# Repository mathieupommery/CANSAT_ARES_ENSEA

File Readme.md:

# Projet 2A CanSat 2024-2025 🚀

## Table des Matières

- [Introduction](#introduction)
- [Équipe](#équipe)
- [Journal de bord](#journal-de-bord)
   - [Objectifs](#objectifs)
- [Livrable](#livrables)
   - [PCB](#pcb)
   - [Station sol](#station-sol)

---

## Introduction
- Il s'agit d'un projet de 2e année d'école d'ingénieur en électronique à l'[ENSEA](https://www.ensea.fr/fr) à Cergy.
- Le but étant de réaliser - pour la **compétition CanSat** organisée par **Planète Sciences et le CNES** - un satellite en forme de canette.
- Celui-ci devra **réaliser plusieurs missions** lorsqu'il sera **lâché d'un drone à environ 120m de hauteur devant un jury**.
- Le projet consiste à faire la **conception** et la **fabrication** de ce satellite.
   - Partie électronique
   (PCB, capteurs, alimentation, station au sol,... )
   - Partie mécanique
   (Châssis, taille, matériau,... )
   - Partie résultats
   (Exploitation des mesures, les mettre en forme en développant ou non une interface, les présenter devant le jury,... )
- Les 4 missions principales imposées en plus du règlement sont :
   - **Mission 1 : Séparation & Transmission**
      - Le CanSat doit se séparer en deux parties à une altitude comprise entre 40 et 60 mètres.​
      - La chaîne de séparation doit résister à une traction de 30N.​
      - Transmission : ​une des parties du CanSat doit transmettre l'altitude et une donnée sur l'atmosphère en temps réel vers une station sol.
   - **Mission 2 : Rétrécissement​**
      - Réduire le CanSat au format 33 cl vous permettra de multiplier votre score par 2 sur la partie technique.
   - **Mission 3 : Instrumentation cassée​**
      - Trouvez un moyen de déterminer votre altitude à partir d'un capteur autre qu'un altimètre barométrique ou un GPS.
   - **Mission 4 : Distance​**
      - Intégrez de quoi mesurer la distance entre les deux parties du CanSat et la communiquer par télémétrie vers la station sol.
      - La Mission 3 n'intervient pas ici.

## Équipe

<div align="center">

   **🙋‍♂️ [Hugo CARVALHO FONTES](https://github.com/HugouShare)**

   **🙋‍♂️ [Louis VOZZOLA](https://github.com/louisvoz57700)**

   **🙋‍♂️ [Nelven THÉBAULT](https://github.com/NelvTheb)**

   **🙋‍♂️ [Mathieu POMMERY](https://github.com/mathieupommery)**

   **🙋‍♂️ [Younés BEN AMEUR](https://github.com/younsben)**

</div>

## Journal de bord

### Présentation orale
- Vous pouvez trouver ici le lien en consultation de l'ensemble de nos [présentations orales](https://enseafr-my.sharepoint.com/:p:/g/personal/nelven_thebault_ensea_fr/EQFq_InugDZNr_ZuubaXSGAB7BGOFKGy7X5Re6X6XMLlZA?e=Kv3kp6)

### Objectifs

| Date       | Objectif                                                                          | Check      |
|------------|-----------------------------------------------------------------------------------|------------|
| 17-09-2024 | Définir les objectifs du projet, planifier et organiser les tâches                | ✅ Terminé |
| 23-10-2024 | Schématique et routage fini → Commander le PCB V0                                 | ✅ Terminé |
| 27-04-2025 | Livrable : Prototype CanSat Fonctionnel + Git final (manque partie communication) | ✅ Terminé |

### Séance 1, 17/09/24
- Organisation du projet et son déroulement
- Planification des livrables et définition des tâches
- Capteurs
   - 6 axes --> branchements OK, code OK, fonctionnement OK
   - baromètre --> prise en main : fonctionnement & branchements
   - thermomètre --> compréhension de la datasheet
### Séance 2, 24/09/24
- Modélisation CanSat 3D V0
- Prise en main du GPS
- Baromètre : écriture du code permettant de récupérer les données et les afficher
- Prise en main du thermomètre et tentative d'afficher la température
### Séance 3, 01/10/24
- Modifications modèle 3D
- Prise en main du module radio
- Avancement PCB
- Baromètre : finalisation du code permettant de récupérer les données et les afficher
- Affichage de la température
### Séance 4, 08/10/24
- 1er Passage oral
   - point sur la progression du projet
- Avancement PCB
### Séance 5, 15/10/24
- Visio (10/10/24) avec l'organisation du CanSat → nouvelles règles
- Redéfinition du projet et des tâches
- Intégration de la RPi 5 dans le projet 
   - Objectif : récupérer l'ensemble de données du CanSat et pouvoir les afficher et les extraire.

### Séance 6, 22/10/24
- Test du module Tarvos-III:

Nous avons essayé de faire communiquer l'EV-Board du Tarvos-III avec son antenne USB. Cependant nous n'avons pas réussi, en identifiant les 2 parties, on se rend vite compte d'un problème sur l'EV-Board car lorsqu'on lui envoie des informations (par exemple sa réinitialisation) la carte ne répond pas. Il y a sûrement un composant HS sur l'EV-Board.
- Vérification et commande du PCB V0
- Avancement sur le module radio
- Test sur servo via contrôle PWM
- RPi5 : Génération d'une trame UART générée par STM32L476RG
- Schéma fonctionnel de la V0 :

### Séance 7, 05/11/24
- Modélisation 3D Cannette et PCB
- RPi5 : Récupération d'une trame UART (générée par STM32L476RG) et affichage dans le terminal
- Avancement du module radio
   - Problème détecté sur l'EV-kit du Tharvos III (plus de réponse)
- Commencer la mise en commun des codes dans le Git
- Réception des PCBs
   - Main board
   - GPS et Radio
- Commande d'un nouveau Tharvos III et des composants du PCB
- Finalisation de la partie code du servomoteur
### Séance 8, 12/11/24
- 2e passage oral
   - MAJ du CdC
   - Présentation du PCB V0 (MAJ) reçu
   - Mise en forme de la stratégie de code
   - Présentation de la modélisation de la partie châssis et du mécanisme de verrouillage
   - Présentation de l'avancement sur la rPi 5
   - Présentation du travail sur le servomoteur
- En attente des composants pour commencer soudure et pour continuer sur le Tharvos III
- RPi5 : Récupération d'une trame UART (générée par STM32L476RG) et affichage dans le terminal
- Avancement sur le code de la mainboard et de certains capteurs

### Séance 9, 19/11/24
- RPi5 : Écriture du code permettant la mise en forme des données UART reçues
- Amélioration de la mise en forme code pour le 6 axes
- Simulation Python de la chute de la canette
- Mécanique : Réalisation de la fermeture permettant aux 2 parties du CANSAT de se séparer.

### Séance 10, 26/11/24
- Soudure des composants sur les sensors PCBs
   - Tarvos III
   - GPS

### Séance 11, 03/12/24
- 3e passage oral
- Test du nouveau servomoteur
- Début modélisation 3D de la station sol
- Changement de la simulation python selon les conseils du jury.

### Séance 12, 10/12/24
- Avancement programmation station sol Qt
- Test du système de verrouillage sur la canette entière
- Soudage du PCB avec la partie accéléromètre
- Modélisation Station sol

### Séance 13, 14/01/25
- Réunion mise au point de l'avancée du projet et nouvelles tâches assignées 
- Avancement programmation station sol Qt + traitement des problèmes softwares
- Début de l'implémentation du code sur la mainboard
- Capteur laser pour mesurer la distance
   - Démontage d'un capteur de 50m pour l'adapter au CanSat

### Séance 14, 21/01/25
<div style="display: flex; justify-content: space-between;">

</div>

- 3D station sol -> intégration dans le châssis des emplacements pour l'électronique
- Recherches sur un télémètre laser viable pour le projet (Mission 3)
- Réadaptation de l'interface graphique Qt + développement software station sol
- Réalisation d'un code pour envoyer une trame et en recevoir une en DMA sur le module de communication (Tarvos III)
- Début de la création de la machine à état avec pour l'instant un échantillonnage des capteurs tous les 0.25s et de l'envoi des données toutes les secondes
- Impression de la cannette avec les modifications faites

### Séance 15, 28/01/25

- Présentation orale
   - Retours :
      - Faire plus concis (20min max)
      - Attention à la visibilité du code et en réduire la quantité montrée
      - Respecter la table des matières
      - Changer la police
   - Objectifs pour le prochain oral :
      - Commencer traitement des données du 6 axes en plus du Radio/GPS 
      - Imprimer des parties de la station sol
      - Tester la vitesse de chute et la résistance du CanSat
      - Finir la soudure de la mainboard
      - Refaire carte GPS plus carte écran led.
      - Tests avec la Tarvos III & Raspberry Pi 5
      - Avoir fait un choix pour le capteur de distance et l'avoir commandé (si besoin)
      - Faire fonctionner le baromètre
- Station sol
   - L'épaisseur des murs a été baissée
   - Prêt à être imprimé
- Test de la mesure de distance via RSSI intégré au module radio Tharvos III
   - On abandonne donc l'idée du capteur laser pour mesurer la distance
<div style="display: flex; justify-content: space-between;">

### Séance 16, 04/02/25
- Impression de la station sol + CanSat détaillé
- Nous continuons à implémenter le code sur notre mainboard
- Travail sur le software station sol
- Soudure de la main board
- Préparation pour première démo (partiellement fonctionnelle) pour
   - Portes ouvertes de l'ENSEA le 08/02/25
   - Réunion d'avancement sur le CanSat sur Paris avec l'organisation du concours le 09/02/25
### Séance 17, 28/01/25

- Nous cherchons des parachutes cohérents pour nos deux parties, donc des parachutes qui permettent une vitesse de descente comprise entre 2m/s et 15m/s, il nous en faut donc deux, un pour le tout, un autre pour le bas, d'un poids de respectivement 300gr et 150gr, on choisit donc les parachutes en 28' 14' et 18' afin de faire des tests:
- [Sierrafoxhobbies](https://www.sierrafoxhobbies.com/fr/parachute/2301-parachute-cansat-xchute-cs.html)

### Séance 18, 11/02/25
- Finalisation du programme de la station sol + validation 
- Commande parachute et connecteurs pour la station sol
- MAJ du modèle 3D de la station sol
- Soudures pour le bouton et l'afficheur de la batterie pour la station sol
- Modification du mécanisme pour réduire les frottements + impression et validation du test
- Montage du mécanisme complet et test du mécanisme avec canette fermée, Test concluant ✅

### Séance 19, 04/03/25
- 5e passage oral
   - Mieux sur la gestion du temps mais toujours au-dessus de 20min (à cause des questions et échanges)
   - Sinon le reste des remarques a été corrigé.
   - Objectifs pour la prochaine séance
      - Avoir un POC (proof of concept) fonctionnel
      - Pouvoir utiliser la station sol
      - Avoir commencé le Poster du CanSat (requis pour la compétition)
- Nouvelles soudures/électronique pour la station sol
   - Réglage d'un problème de connexion lié à une couche du PCB arrachée au niveau du bouton
   - Changement pour des câbles plus souples
   - Arrivée et bon fonctionnement des nappes en molex avec connectiques interchangeables pour $`\mu`$HDMI/HDMI et $`\mu`$USB/USB pour la Raspberry Pi 5

### Séance 20, 11/03/25
- Station sol
   - Modification du bouton général par un plus joli avec LED
   - Découpe au laser d'une planche en MDF pour faire la face du dessus de la station sol
   - Réarrangement des pièces et impression finale - si tout marche bien lors de la prochaine séance - des pièces
- 1er test du CanSat
   - Test concluant du parachute en larguant le CanSat d'un drone à environ 30-50 m, reste à valider la vitesse de chute
- Poster de projet
   - Nous avons commencé l'affiche du projet (nécessaire pour la compétition), choix du support : feuille A3 en $`\LaTeX`$

## Séance 21, 18/03/25
- Station sol
   - Modélisation et impression des finitions 
   
- Canette
   - Ajout de fonctions (servomoteur) sur le bouton : appui simple -> verrouille ; appui long libère
   - Problème sur la liaison ST-Link avec le PCB, problèmes pour téléverser le code
- Software
   - Amélioration code existant pour la station sol  
   - Optimisation du code et mise en place d'un bouton pour que lorsqu'on appuie, les 2 parties soient libérées, et un appui long, le mécanisme se referme
   - Test du baromètre et mise en place du code pour l'ouverture du Cansat à une certaine distance (testé et validé)
     
- Canette
   - En fin de séance, nous avons testé l'ouverture du cansat avec déploiement du second parachute

### Séance 22, 25/03/25
- Station sol
  - Derniers ajustements du code de la station sol
  - Essais & Validations
- Stockage
   - modélisation et impression boîte pour les tharvos III
- Canette
   - Identification des problèmes liés au pcb (mauvaises résistances, ...)
   
### Séance 23, 01/04/25
- Présentation du POC

### 11/04/25  
- Soudure de cartes de secours
- Réalisation de deux modèles CanSat pour le jour J  

# Livrables
## PCB
<div style="display: flex; justify-content: space-between;">

</div>

  Mainboard, pcb 6 couches avec:
  * accéléromètre
  * stm32g431cbu6
  * régulateur buck 6-28v vers 5v
  * 2 ldo 5v vers 3.3v dont 1 activable sur commande du MCU.
  * port de carte micro sd
  * 2 ports uart dédiés
  * port servo dédié
  * pads de soudures pour accessoires et debug(swd)

    ### V1:

    ### V2:

* Capteur de courant enlevé car peu utile.
* Baromètre bmp581 précision relative:+/-2cm ! 
* connecteur carte à carte 10 et 12 contacts pour une réduction de la place !
* carte principale avec carte auxiliaires flexibles.

### Carte auxiliaire flexible:

   * Module radio tarvos.
   * module gps pa1010d.
   * connexion swd rapide avec bouton de gestion des modes.
   * Double témoin lumineux adressable 16 millions de couleurs.
   * connecteur 2 broches pour connecter l'indicateur de largage.

Carte auxiliaire flexible + mainboard flexible installée dans la partie haute du CanSat :

### Suite à de nombreux problèmes longs à débugger:
   ### V3:

* Connecteurs plus robustes
* Connecteur de la batterie déporté
* Servomoteur uniquement soudé

* But: revenir à un design plus simple et robuste avec des connecteurs plus gros, tout en gardant le design esthétique et le plus fonctionnel et robuste.
## PCB sensor Vfinale:

   * Nous avons donc sorti le baromètre
   * Design plus simple mais robuste
   * Uniquement des soudures ou connecteurs robustes
   * Debug beaucoup plus rapide
   * Modulaire
   * Beaucoup de fonctionnalités.

## Station Sol
### Boîtier et électronique
   
   Spécifications :
   - Raspberry Pi 5 intégré
   - Module radio Tarvos III (Würth Elektronik)
   - Écran tactile 7" connecté au Raspberry Pi 5
   - Batterie Li-Ion de 20 000 mAh avec BMS et prises intégrées
   - Indicateur de charge et de niveau de la batterie
   - Prise USB-C (femelle) de 9V⎓2A (18W) pour la recharge de la batterie
   - Bouton ON/OFF (LED allumée lorsque la rPi 5 est sous tension)
   - Emplacement dédié pour ranger le CanSat
   - Emplacement pour le parachute
   - Châssis interne imprimé en 3D en PLA
   - Façade en MDF découpée et gravée au laser
   - Accès simplifié à l'intérieur de la boîte grâce aux vis à main (capuchons noirs)

   Fichier 3D aller dans `./Hardware/Fichier%203D%20Station%20sol/` :
   - Fichier global avec tout l'historique : `Case.f3z`
   - Pour impression, découpage en 3 prints pour le châssis : `Case G.stl`,`Case D.stl`, `Range cable.stl`
   - Pour la découpe laser de la planche en bois : `Plaque bois Cansat_laser.dxf`
   - Le reste, caches et contours sont pour la finition
## Mécanique
Voici la version finale de la mécanique présente sur notre CANSAT.

### Software

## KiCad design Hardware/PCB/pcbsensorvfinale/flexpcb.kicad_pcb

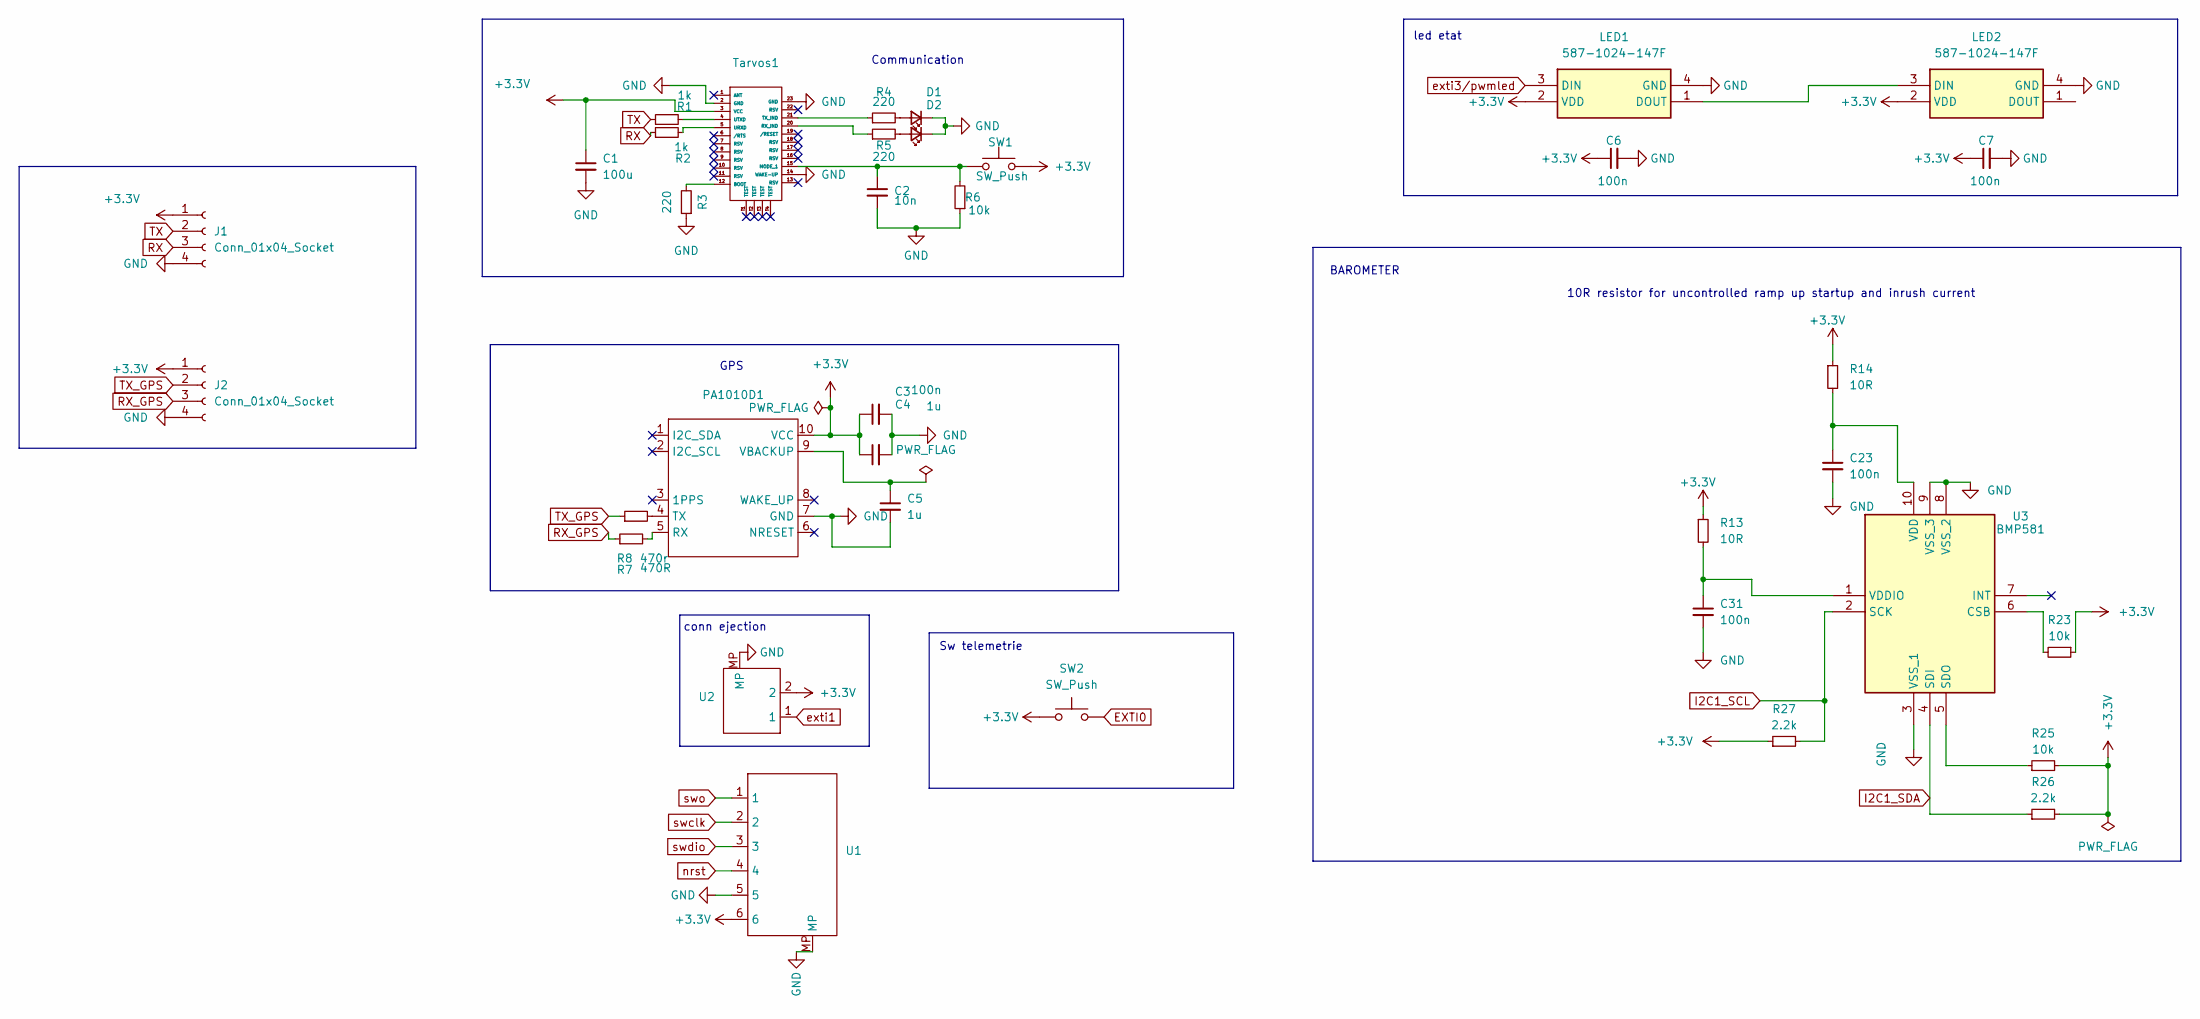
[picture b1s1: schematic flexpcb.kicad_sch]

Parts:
C1: 100u; C_1206_3216Metric
C2: 10n; C_0402_1005Metric
C3, C6, C7: 100n; C_0402_1005Metric
C4: 1u; C_0402_1005Metric
C5: 1u; C_0402_1005Metric_Pad0.74x0.62mm_HandSolder
C23, C31: 100n; C_0402_1005Metric_Pad0.74x0.62mm_HandSolder
D1, D2: LED_Small; LED_0603_1608Metric
J1: Conn_01x04_Socket; JST_SH_BM04B-SRSS-TB_1x04-1MP_P1.00mm_Vertical
J2: Conn_01x04_Socket; JST_SH_SM04B-SRSS-TB_1x04-1MP_P1.00mm_Horizontal
LED1, LED2: 587-1024-147F; 5871024147F; Manufacturer_Part_Number 587-1024-147F
PA1010D1: PA1010D
R1, R2: 1k; R_0402_1005Metric
R3, R4, R5: 220; R_0402_1005Metric
R6: 10k; R_0402_1005Metric
R7: 470R; R_0402_1005Metric
R8: 470r; R_0402_1005Metric
R13, R14: 10R; R_0402_1005Metric_Pad0.72x0.64mm_HandSolder
R23, R25: 10k; R_0402_1005Metric_Pad0.72x0.64mm_HandSolder
R26, R27: 2.2k; R_0402_1005Metric_Pad0.72x0.64mm_HandSolder
SW1: SW_Push; PinHeader_1x02_P1.00mm_Horizontal
SW2: SW_Push; SW_Push_1P1T_NO_CK_PTS125Sx43PSMTR
Tarvos1: Tarvos III
U1: JST_SH_BM06B-SRSS-TB_1x06-1MP_P1.00mm_Vertical
U2: JST_SH_BM02B-SRSS-TB_1x02-1MP_P1.00mm_Vertical
U3: BMP581; Manufacturer_Part_Number BMP581; Mouser Part Number 262-BMP581

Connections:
+3.3V: C1.1, C3.1, C4.1, C6.1, C7.1, J1.1, J2.1, LED1.2 (VDD), LED2.2 (VDD), PA1010D1.10 (VCC), R13.1, R14.1, R23.1, R25.2, R26.2, R27.1, SW1.2, SW2.1, Tarvos1.3 (VCC), U1.6, U2.2
EXTI0: SW2.2
GND: C1.2, C2.2, C3.2, C4.2, C5.2, C6.2, C7.2, C23.2, C31.2, D1.1 (K), D2.1 (K), J1.4, J1.MP, J2.4, J2.MP, LED1.4 (GND), LED2.4 (GND), PA1010D1.7 (GND), R3.1, R6.1, Tarvos1.2 (GND), Tarvos1.14 (WAKE-UP), Tarvos1.23 (GND), U1.5, U1.MP, U2.MP, U3.3 (VSS_1), U3.8 (VSS_2), U3.9 (VSS_3)
I2C1_SCL: R27.2, U3.2 (SCK)
I2C1_SDA: R26.1, U3.4 (SDI)
unnamed: D1.2 (A), R4.2
unnamed: D2.2 (A), R5.2
unnamed: LED1.1 (DOUT), LED2.3 (DIN)
unnamed: PA1010D1.5 (RX), R7.2
unnamed: PA1010D1.4 (TX), R8.2
unnamed: C5.1, PA1010D1.9 (VBACKUP)
unnamed: R3.2, Tarvos1.12 (BOOT)
unnamed: C2.1, R6.2, SW1.1, Tarvos1.15 (MODE_1)
unnamed: R5.1, Tarvos1.20 (RX_IND)
unnamed: R4.1, Tarvos1.21 (TX_IND)
unnamed: R2.2, Tarvos1.5 (URXD)
unnamed: R1.2, Tarvos1.4 (UTXD)
unnamed: R23.2, U3.6 (CSB)
unnamed: R25.1, U3.5 (SDO)
unnamed: C23.1, R14.2, U3.10 (VDD)
unnamed: C31.1, R13.2, U3.1 (VDDIO)
RX: J1.3, R2.1
RX_GPS: J2.3, R7.1
TX: J1.2, R1.1
TX_GPS: J2.2, R8.1
exti1: U2.1
exti3/pwmled: LED1.3 (DIN)
nrst: U1.4
swclk: U1.2
swdio: U1.3
swo: U1.1

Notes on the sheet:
conn ejection
BAROMETER
Sw telemetrie
GPS
led etat
10R resistor for uncontrolled ramp up startup and inrush current
Communication

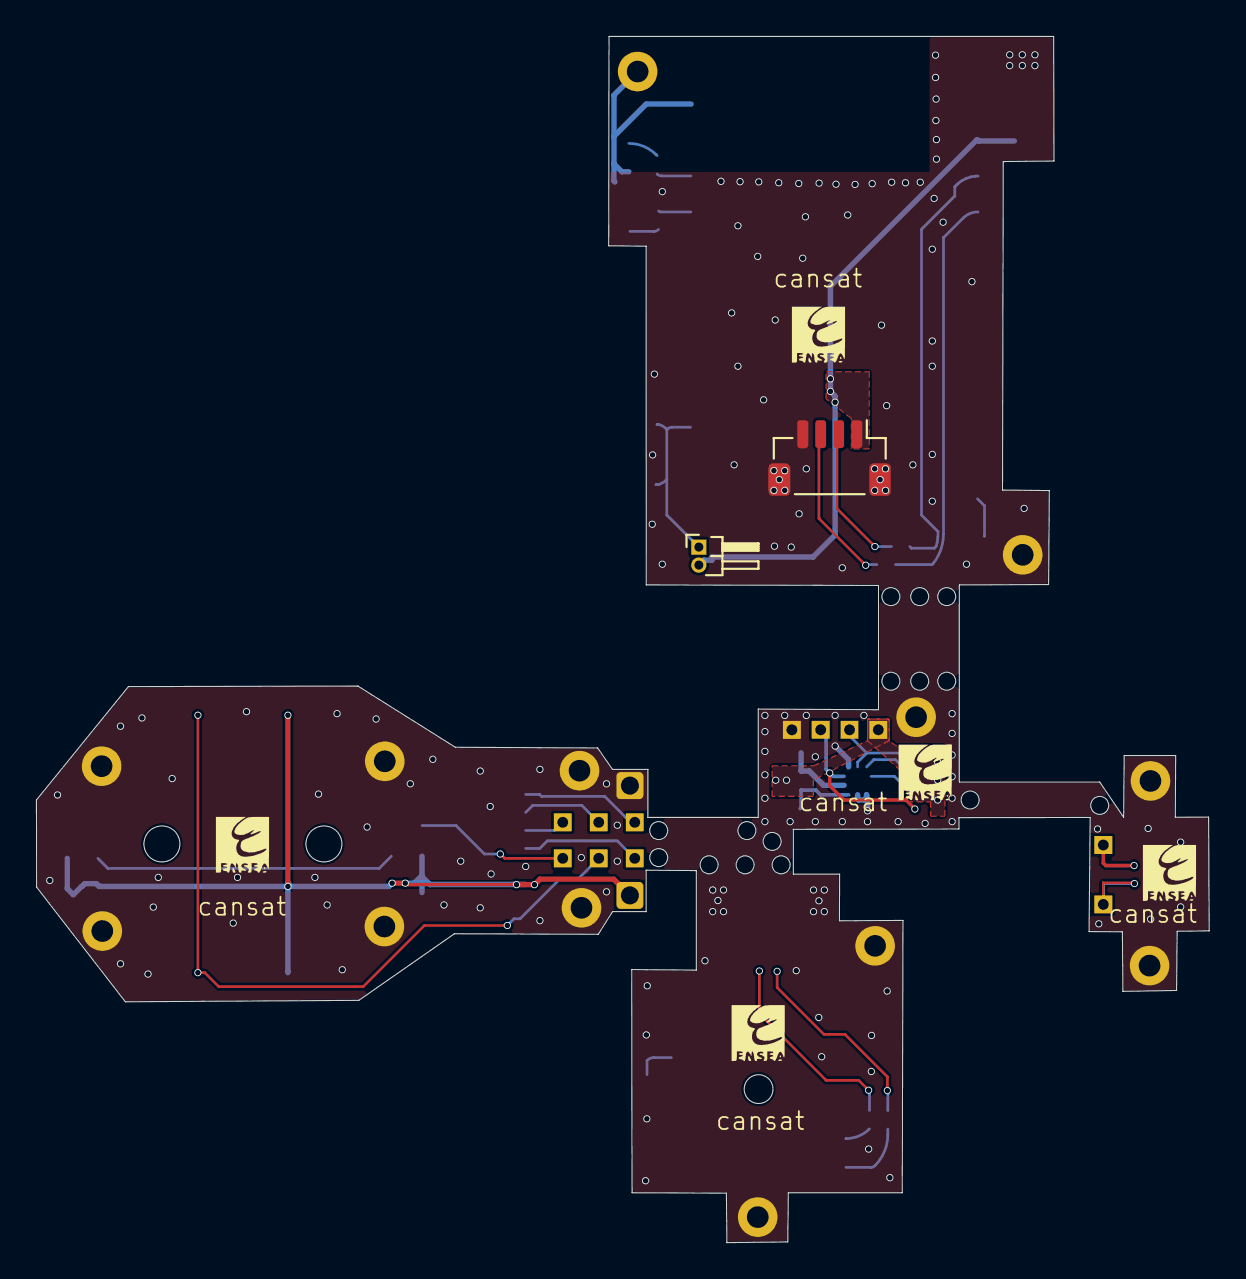
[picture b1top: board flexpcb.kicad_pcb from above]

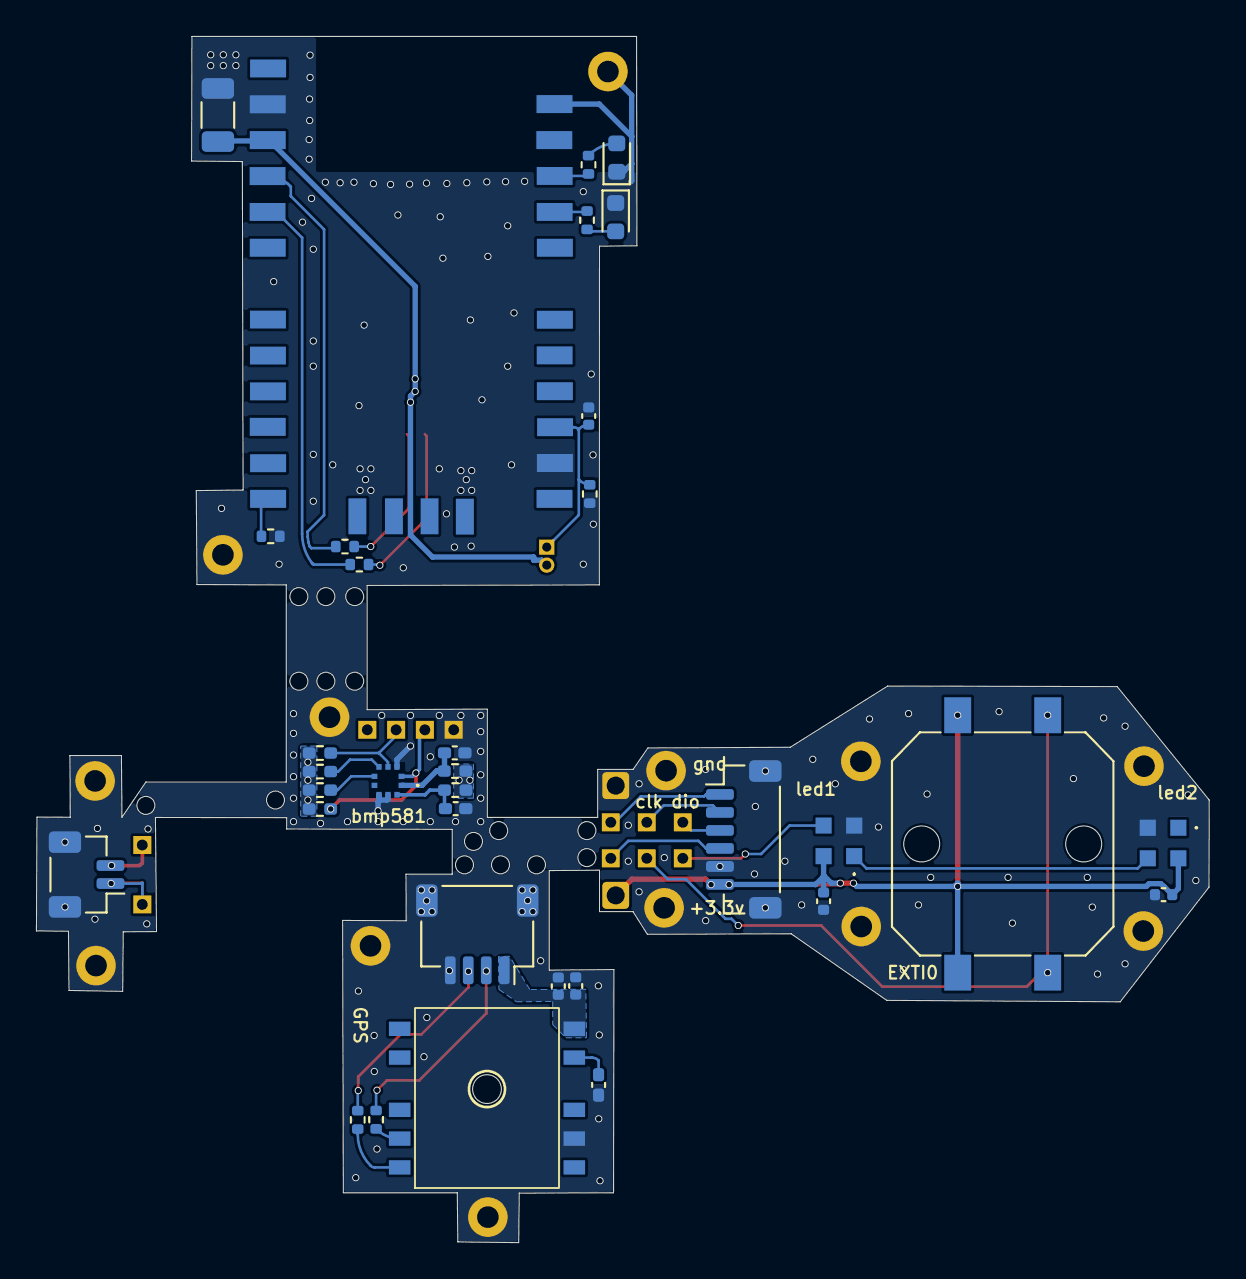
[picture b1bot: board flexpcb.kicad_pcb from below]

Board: 2 copper layers, 65.2 x 67.0 mm, 36 parts (34 on the bottom side), 24 nets.

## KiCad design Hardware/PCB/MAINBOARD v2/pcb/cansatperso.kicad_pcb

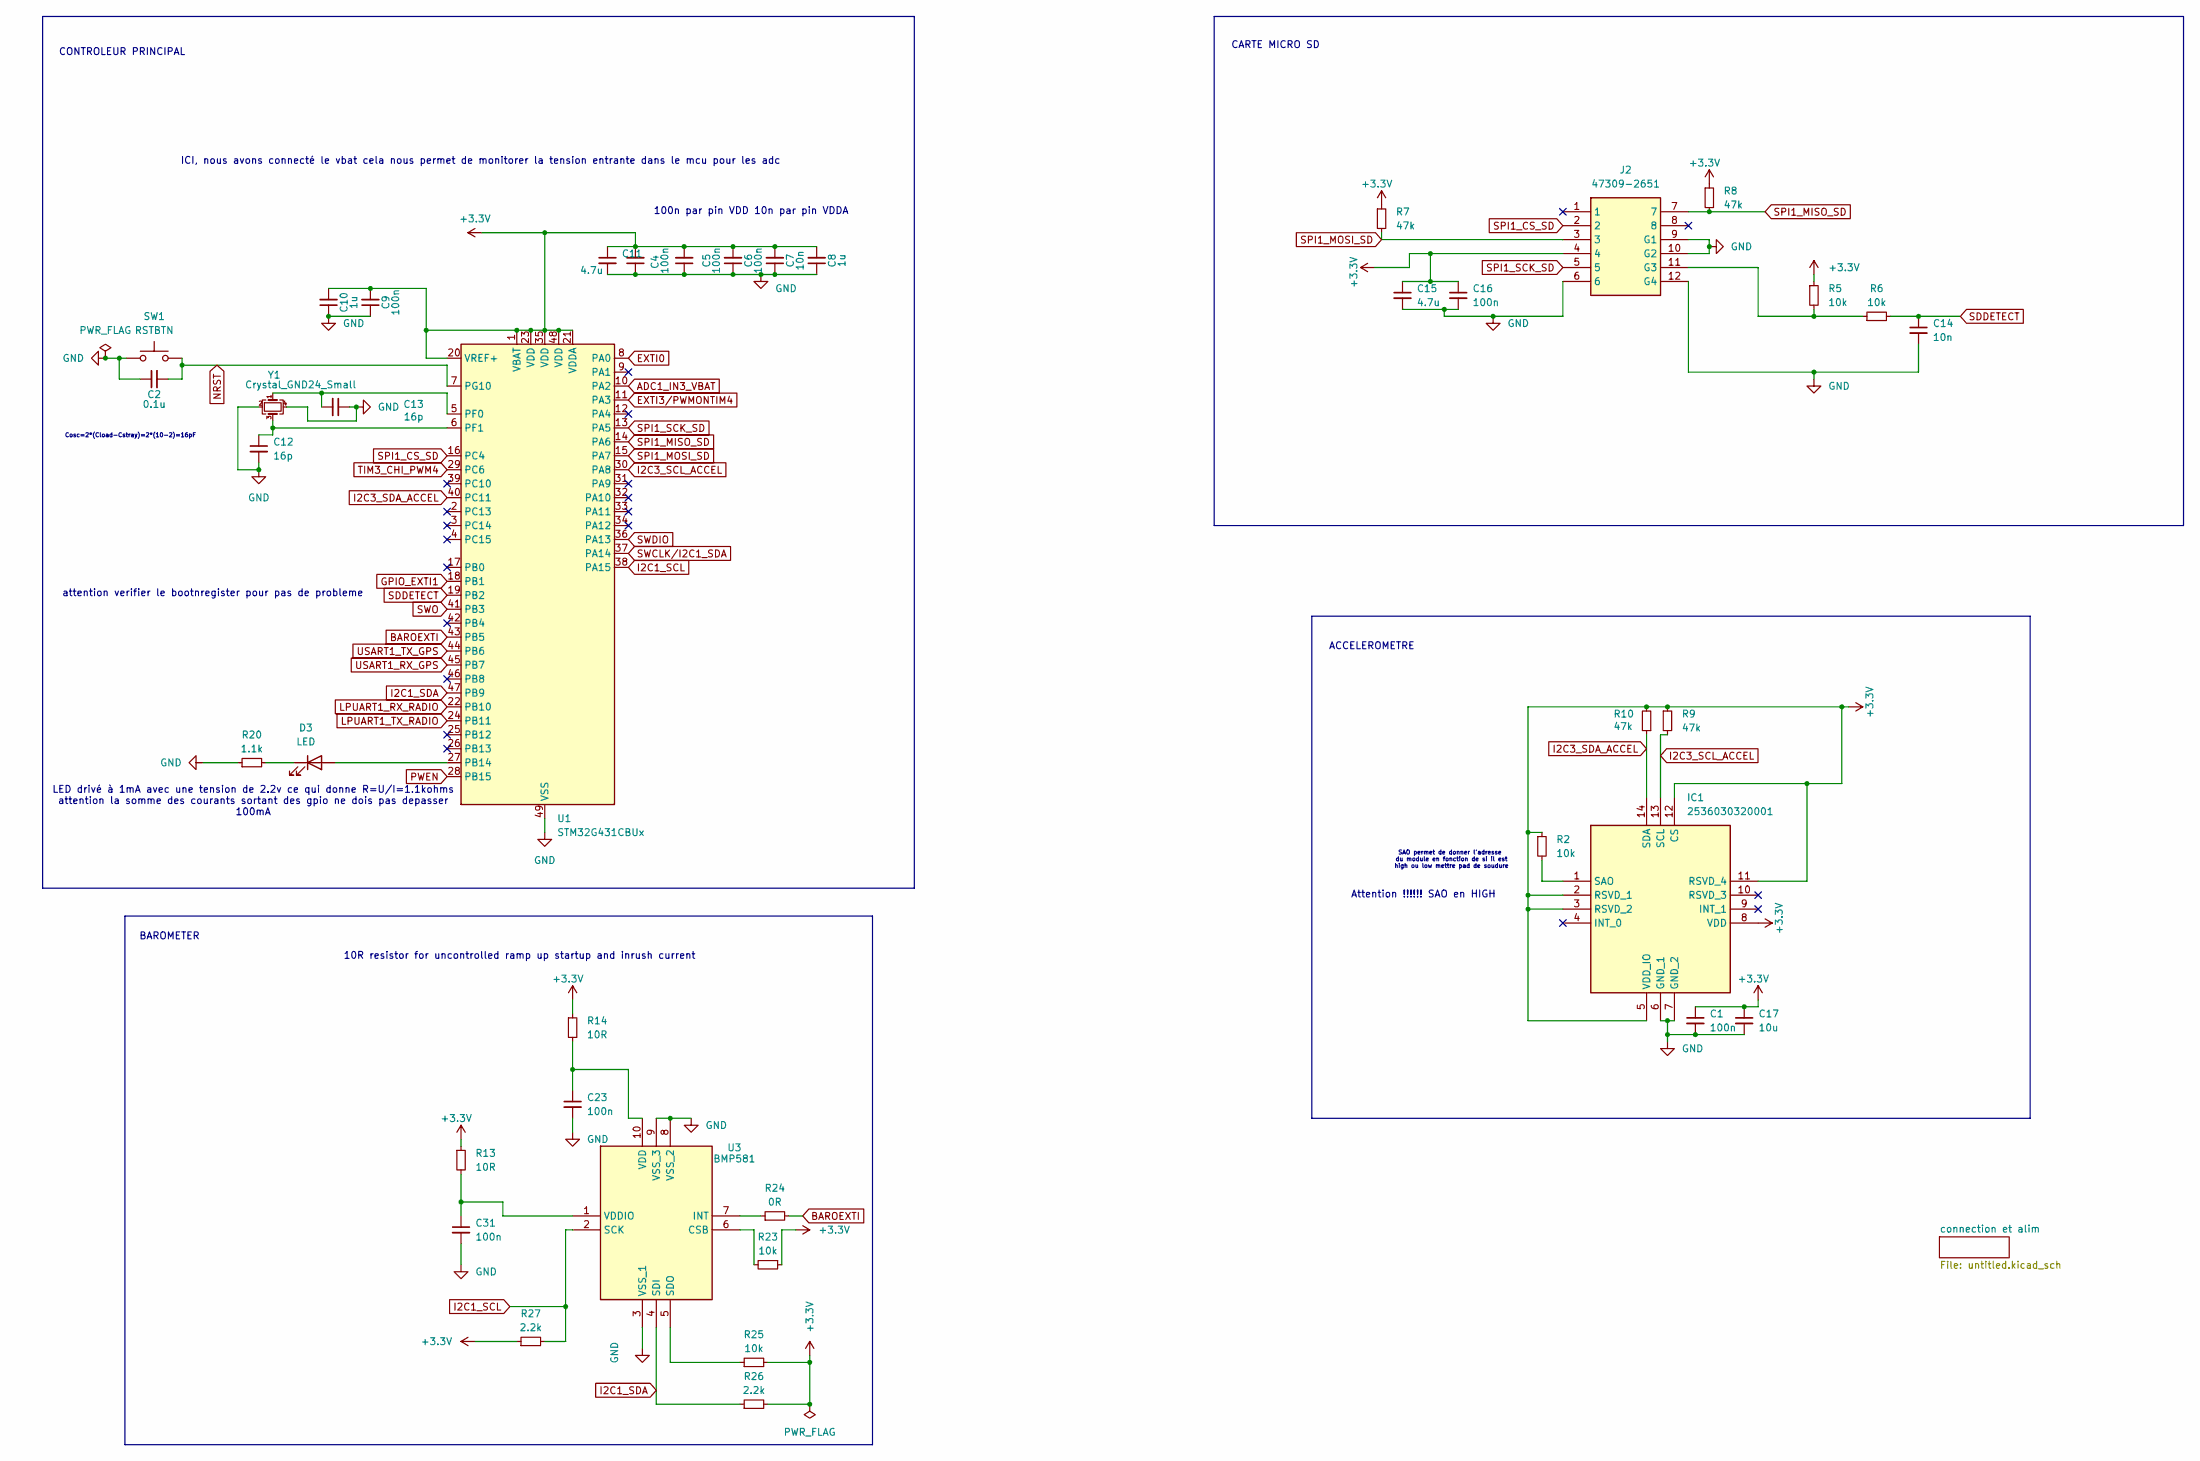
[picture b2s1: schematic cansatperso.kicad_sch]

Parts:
C1, C4, C5, C6, C9, C16, C23, C31: 100n; C_0402_1005Metric_Pad0.74x0.62mm_HandSolder
C2: 0.1u; C_0402_1005Metric_Pad0.74x0.62mm_HandSolder
C7, C14: 10n; C_0402_1005Metric_Pad0.74x0.62mm_HandSolder
C8, C10: 1u; C_0402_1005Metric_Pad0.74x0.62mm_HandSolder
C11, C15: 4.7u; C_0402_1005Metric_Pad0.74x0.62mm_HandSolder
C12, C13: 16p; C_0402_1005Metric_Pad0.74x0.62mm_HandSolder
C17: 10u; C_0402_1005Metric_Pad0.74x0.62mm_HandSolder
D3: LED; LED_0603_1608Metric_Pad1.05x0.95mm_HandSolder
IC1: 2536030320001; Manufacturer_Part_Number 2536030320001; Mouser Part Number 710-2536030320001
J2: 47309-2651; Manufacturer_Part_Number 47309-2651
R2, R5, R6, R23, R25: 10k; R_0402_1005Metric_Pad0.72x0.64mm_HandSolder
R7, R8, R9, R10: 47k; R_0402_1005Metric_Pad0.72x0.64mm_HandSolder
R13, R14: 10R; R_0402_1005Metric_Pad0.72x0.64mm_HandSolder
R20: 1.1k; R_0402_1005Metric_Pad0.72x0.64mm_HandSolder
R24: 0R; R_0402_1005Metric_Pad0.72x0.64mm_HandSolder
R26, R27: 2.2k; R_0402_1005Metric_Pad0.72x0.64mm_HandSolder
SW1: RSTBTN; SW_KXT3
U1: STM32G431CBUx; QFN-48-1EP_7x7mm_P0.5mm_EP5.6x5.6mm
U3: BMP581; Manufacturer_Part_Number BMP581; Mouser Part Number 262-BMP581
Y1: Crystal_GND24_Small; MCSJK7U1200101080B10

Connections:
+3.3V: C1.1, C4.2, C5.2, C6.2, C7.2, C8.2, C9.2, C10.2, C11.1, C15.1, C16.1, C17.1, IC1.2 (RSVD_1), IC1.3 (RSVD_2), IC1.5 (VDD_IO), IC1.8 (VDD), IC1.11 (RSVD_4), IC1.12 (CS), J2.4, R2.1, R5.1, R7.1, R8.1, R9.1, R10.2, R13.1, R14.1, R23.1, R25.2, R26.2, R27.1, U1.1 (VBAT), U1.20 (VREF+), U1.21 (VDDA), U1.23 (VDD), U1.35 (VDD), U1.48 (VDD); also elsewhere on the board
ADC1_IN3_VBAT: U1.10 (PA2); also elsewhere on the board
BAROEXTI: R24.2, U1.43 (PB5)
EXTI0: U1.8 (PA0); also elsewhere on the board
EXTI3/PWMONTIM4: U1.11 (PA3); also elsewhere on the board
GND: C1.2, C2.1, C4.1, C5.1, C6.1, C7.1, C8.1, C9.1, C10.1, C11.2, C12.2, C13.1, C14.2, C15.2, C16.2, C17.2, C23.2, C31.2, IC1.6 (GND_1), IC1.7 (GND_2), J2.6, J2.9 (G1), J2.10 (G2), J2.12 (G4), R20.1, SW1.1, U1.49 (VSS), U3.3 (VSS_1), U3.8 (VSS_2), U3.9 (VSS_3), Y1.2, Y1.4; also elsewhere on the board
GPIO_EXTI1: U1.18 (PB1); also elsewhere on the board
I2C1_SCL: R27.2, U1.38 (PA15), U3.2 (SCK)
I2C1_SDA: R26.1, U1.47 (PB9), U3.4 (SDI)
I2C3_SCL_ACCEL: IC1.13 (SCL), R9.2, U1.30 (PA8); also elsewhere on the board
I2C3_SDA_ACCEL: IC1.14 (SDA), R10.1, U1.40 (PC11); also elsewhere on the board
LPUART1_RX_RADIO: U1.22 (PB10); also elsewhere on the board
LPUART1_TX_RADIO: U1.24 (PB11); also elsewhere on the board
NRST: C2.2, SW1.2, U1.7 (PG10); also elsewhere on the board
unnamed: D3.2 (A), U1.27 (PB14)
unnamed: D3.1 (K), R20.2
unnamed: IC1.1 (SAO), R2.2
unnamed: J2.11 (G3), R5.2, R6.1
unnamed: C13.2, U1.5 (PF0), Y1.1
unnamed: C12.1, U1.6 (PF1), Y1.3
unnamed: R23.2, U3.6 (CSB)
unnamed: R24.1, U3.7 (INT)
unnamed: R25.1, U3.5 (SDO)
unnamed: C23.1, R14.2, U3.10 (VDD)
unnamed: C31.1, R13.2, U3.1 (VDDIO)
PWEN: U1.28 (PB15); also elsewhere on the board
SDDETECT: C14.1, R6.2, U1.19 (PB2)
SPI1_CS_SD: J2.2, U1.16 (PC4)
SPI1_MISO_SD: J2.7, R8.2, U1.14 (PA6)
SPI1_MOSI_SD: J2.3, R7.2, U1.15 (PA7)
SPI1_SCK_SD: J2.5, U1.13 (PA5)
SWCLK/I2C1_SDA: U1.37 (PA14); also elsewhere on the board
SWDIO: U1.36 (PA13); also elsewhere on the board
SWO: U1.41 (PB3); also elsewhere on the board
TIM3_CHI_PWM4: U1.29 (PC6); also elsewhere on the board
USART1_RX_GPS: U1.45 (PB7); also elsewhere on the board
USART1_TX_GPS: U1.44 (PB6); also elsewhere on the board

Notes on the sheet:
Cosc=2*(Cload-Cstray)=2*(10-2)=16pF
BAROMETER
10R resistor for uncontrolled ramp up startup and inrush current
LED drivé à 1mA avec une tension de 2.2v ce qui donne R=U/I=1.1kohms attention la somme des courants sortant des gpio ne dois pas depasser 100mA
Attention !!!!!! SAO en HIGH
CONTROLEUR PRINCIPAL
CARTE MICRO SD
SAO permet de donner l'adresse du module en fonction de si il est high ou low mettre pad de soudure
ICI, nous avons connecté le vbat cela nous permet de monitorer la tension entrante dans le mcu pour les adc
100n par pin VDD 10n par pin VDDA
ACCELEROMETRE
attention verifier le bootnregister pour pas de probleme

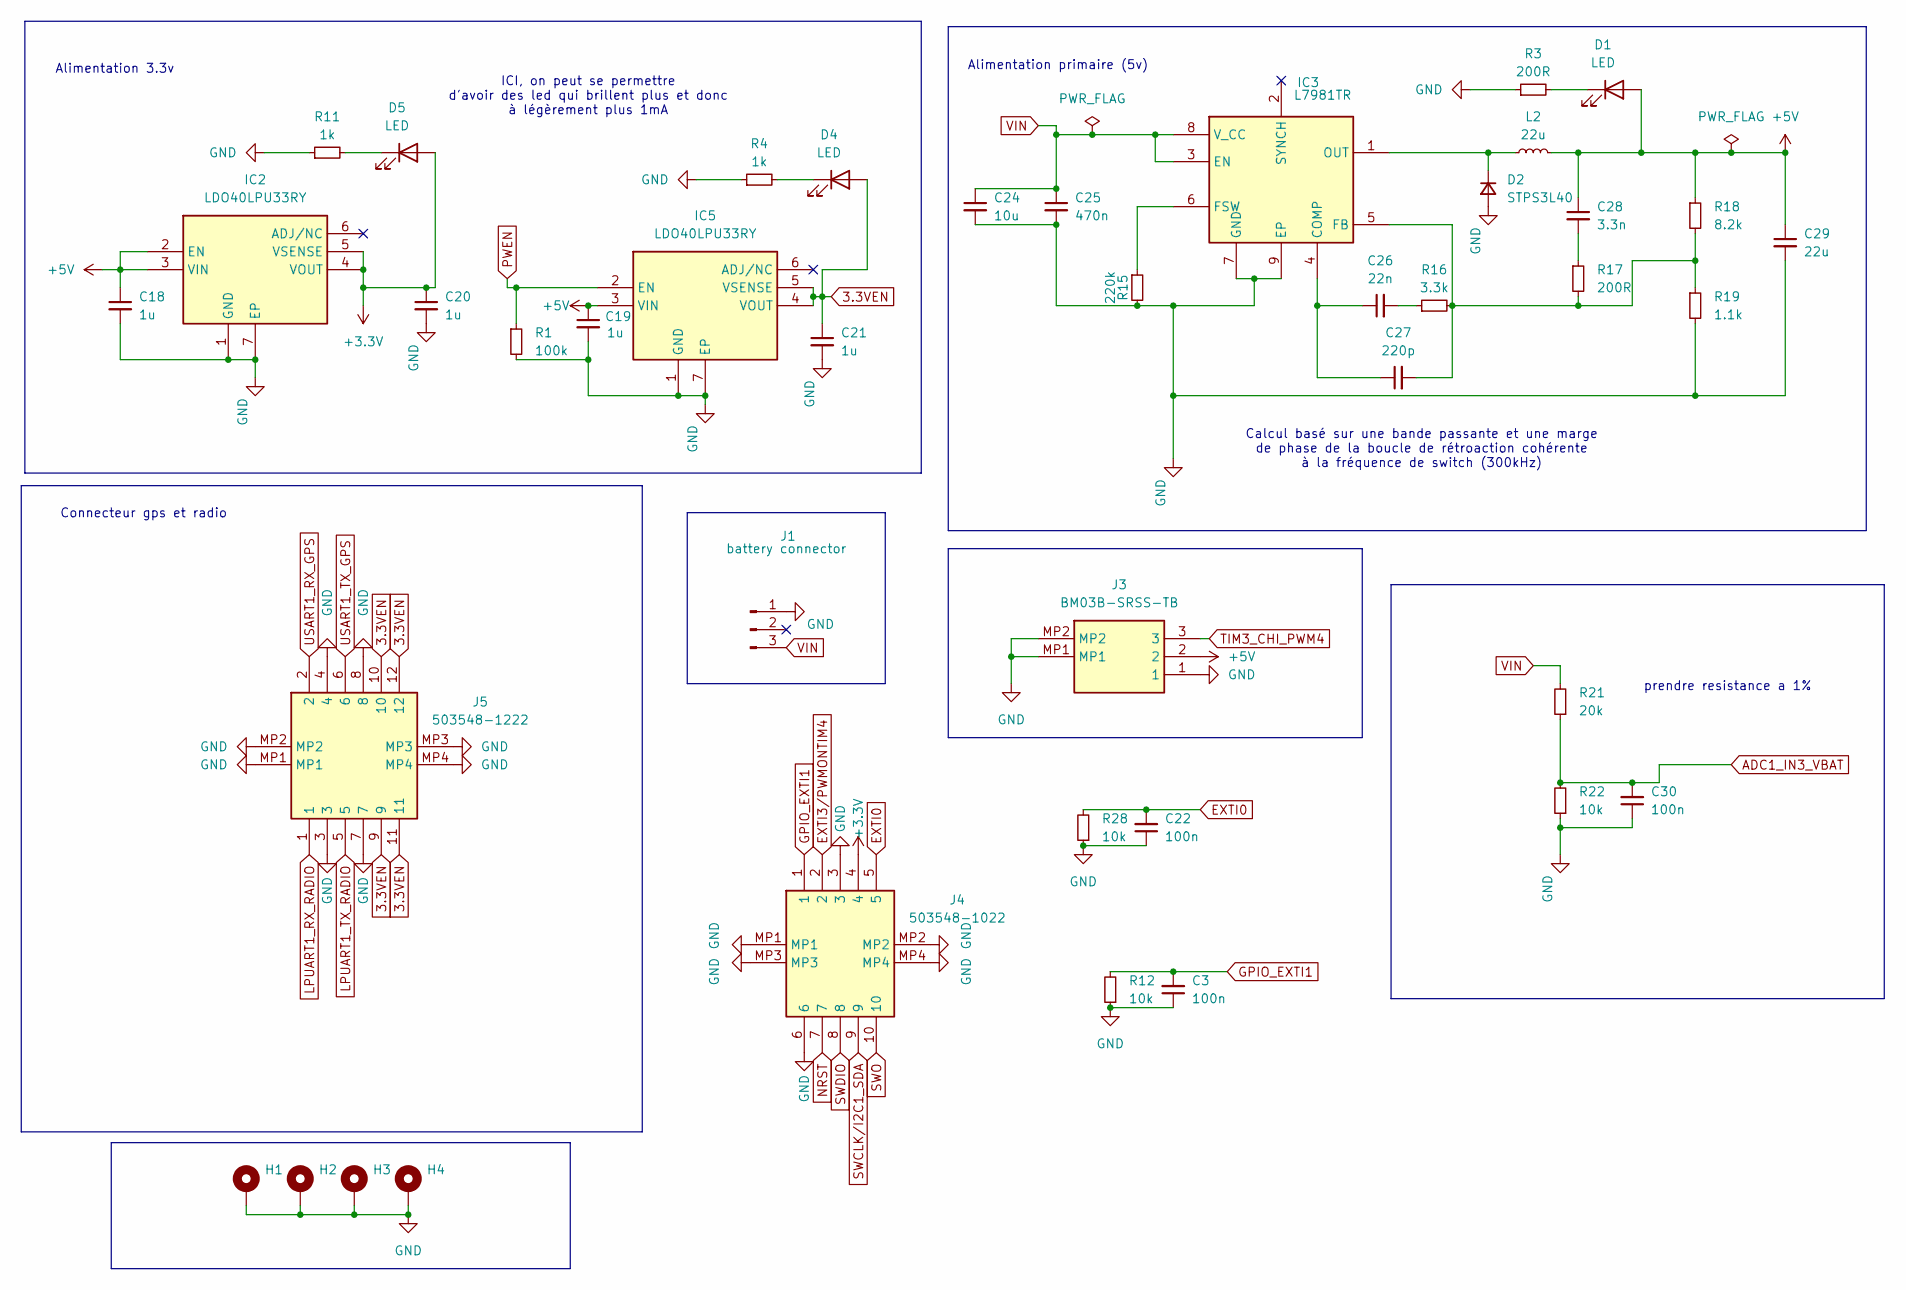
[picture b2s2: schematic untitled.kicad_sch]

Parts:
C3, C22, C30: 100n; C_0402_1005Metric_Pad0.74x0.62mm_HandSolder
C18, C19, C20, C21: 1u; C_0402_1005Metric_Pad0.74x0.62mm_HandSolder
C24: 10u; C_1210_3225Metric_Pad1.33x2.70mm_HandSolder
C25: 470n; C_0402_1005Metric_Pad0.74x0.62mm_HandSolder
C26: 22n; C_0402_1005Metric_Pad0.74x0.62mm_HandSolder
C27: 220p; C_0402_1005Metric_Pad0.74x0.62mm_HandSolder
C28: 3.3n; C_0402_1005Metric_Pad0.74x0.62mm_HandSolder
C29: 22u; C_1210_3225Metric_Pad1.33x2.70mm_HandSolder
D1, D4, D5: LED; LED_0603_1608Metric_Pad1.05x0.95mm_HandSolder
D2: STPS3L40; D_SMB_Handsoldering
H1, H2, H3, H4: MountingHole_Pad; mountinghole1.2mm
IC2, IC5: LDO40LPU33RY; SON95P300X300X90-7N-D; Manufacturer_Part_Number LDO40LPU33RY; Mouser Part Number 511-LDO40LPU33RY
IC3: L7981TR; SON50P300X300X100-9N-D; Manufacturer_Part_Number L7981TR; Mouser Part Number 511-L7981TR
J1: battery connector; JST_XH_B3B-XH-AM_1x03_P2.50mm_Vertical
J3: BM03B-SRSS-TB; JST_SH_BM03B-SRSS-TB_1x03-1MP_P1.00mm_Vertical; Manufacturer_Part_Number BM03B-SRSS-TB; Mouser Part Number N/A
J4: 503548-1022; 5035481022; Manufacturer_Part_Number 503548-1022; Mouser Part Number 538-503548-1022
J5: 503548-1222; 5035481222; Manufacturer_Part_Number 503548-1222; Mouser Part Number 538-503548-1222
L2: 22u; INDPM7373X340N
R1: 100k; R_0402_1005Metric_Pad0.72x0.64mm_HandSolder
R3, R17: 200R; R_0402_1005Metric_Pad0.72x0.64mm_HandSolder
R4, R11: 1k; R_0402_1005Metric_Pad0.72x0.64mm_HandSolder
R12, R22, R28: 10k; R_0402_1005Metric_Pad0.72x0.64mm_HandSolder
R15: 220k; R_0402_1005Metric_Pad0.72x0.64mm_HandSolder
R16: 3.3k; R_0402_1005Metric_Pad0.72x0.64mm_HandSolder
R18: 8.2k; R_0402_1005Metric_Pad0.72x0.64mm_HandSolder
R19: 1.1k; R_0402_1005Metric_Pad0.72x0.64mm_HandSolder
R21: 20k; R_0402_1005Metric_Pad0.72x0.64mm_HandSolder

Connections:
3.3VEN: C21.1, D4.2 (A), IC5.4 (VOUT), IC5.5 (VSENSE), J5.9, J5.10, J5.11, J5.12
+3.3V: C20.1, D5.2 (A), IC2.4 (VOUT), IC2.5 (VSENSE), J4.4; also elsewhere on the board
+5V: C18.1, C19.1, C28.1, C29.1, D1.2 (A), IC2.2 (EN), IC2.3 (VIN), IC5.3 (VIN), J3.2, L2.2, R18.1; also elsewhere on the board
ADC1_IN3_VBAT: C30.2, R21.1, R22.2; also elsewhere on the board
EXTI0: C22.2, J4.5, R28.2; also elsewhere on the board
EXTI3/PWMONTIM4: J4.2; also elsewhere on the board
GND: C3.1, C18.2, C19.2, C20.2, C21.2, C22.1, C24.2, C25.2, C29.2, C30.1, D2.2 (A), H1.1, H2.1, H3.1, H4.1, IC2.1 (GND), IC2.7 (EP), IC3.7 (GND), IC3.9 (EP), IC5.1 (GND), IC5.7 (EP), J1.1, J3.1, J3.MP1, J3.MP2, J4.3, J4.6, J4.MP1, J4.MP2, J4.MP3, J4.MP4, J5.3, J5.4, J5.7, J5.8, J5.MP1, J5.MP2, J5.MP3, J5.MP4, R1.2, R3.1, R4.1, R11.1, R12.1, R15.2, R19.2, R22.1, R28.1; also elsewhere on the board
GPIO_EXTI1: C3.2, J4.1, R12.2; also elsewhere on the board
LPUART1_RX_RADIO: J5.1; also elsewhere on the board
LPUART1_TX_RADIO: J5.5; also elsewhere on the board
NRST: J4.7; also elsewhere on the board
unnamed: C26.2, R16.1
unnamed: C28.2, R17.1
unnamed: D1.1 (K), R3.2
unnamed: D2.1 (K), IC3.1 (OUT), L2.1
unnamed: D4.1 (K), R4.2
unnamed: D5.1 (K), R11.2
unnamed: C26.1, C27.1, IC3.4 (COMP)
unnamed: C27.2, IC3.5 (FB), R16.2, R17.2, R18.2, R19.1
unnamed: IC3.6 (FSW), R15.1
PWEN: IC5.2 (EN), R1.1; also elsewhere on the board
SWCLK/I2C1_SDA: J4.9; also elsewhere on the board
SWDIO: J4.8; also elsewhere on the board
SWO: J4.10; also elsewhere on the board
USART1_RX_GPS: J5.2; also elsewhere on the board
USART1_TX_GPS: J5.6; also elsewhere on the board
VIN: C24.1, C25.1, IC3.3 (EN), IC3.8 (V_CC), J1.3, R21.2

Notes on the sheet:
Alimentation primaire (5v)
Alimentation 3.3v
prendre resistance a 1%
Connecteur gps et radio
ICI, on peut se permettre d'avoir des led qui brillent plus et donc à légèrement plus 1mA
Calcul basé sur une bande passante et une marge de phase de la boucle de rétroaction cohérente à la fréquence de switch (300kHz)

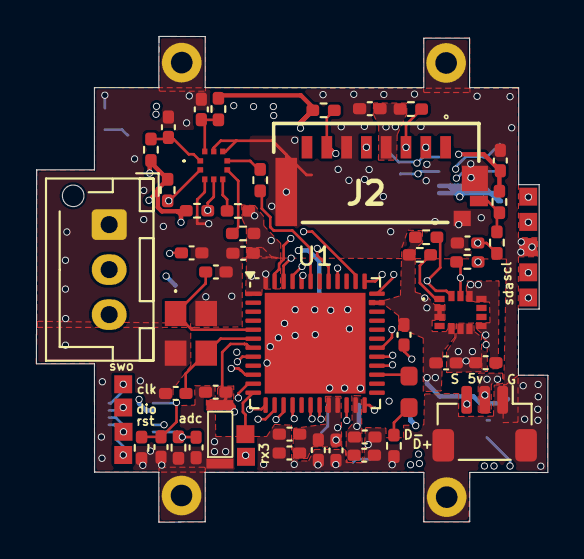
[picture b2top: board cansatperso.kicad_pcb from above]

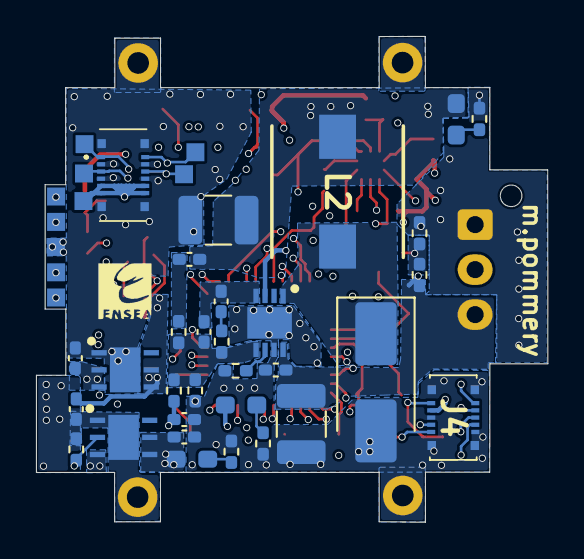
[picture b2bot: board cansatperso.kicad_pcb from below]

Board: 6 copper layers, 28.4 x 27.0 mm, 88 parts (32 on the bottom side), 49 nets.

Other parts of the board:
4, 5, 6, 7, 7#2, 8: (no value)
U2: JST_SH_BM03B-SRSS-TB_1x03-1MP_P1.00mm_Vertical

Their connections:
+3.3V: 7.1, 7#2.1; also elsewhere on the board
+5V: 8.1, U2.2; also elsewhere on the board
GND: 6.1, U2.1, U2.MP; also elsewhere on the board
I2C3_SCL_ACCEL: 4.1; also elsewhere on the board
I2C3_SDA_ACCEL: 5.1; also elsewhere on the board
TIM3_CHI_PWM4: U2.3; also elsewhere on the board
